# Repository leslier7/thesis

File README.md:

# A Comparison of the Arm and RISC-V Architectures on the RP2350 Microcontroller

## Abstract
This thesis compares the M-33 implementation of the Arm ISA with the Hazard3
implementation of the RISC-V ISA on the RP2350 microcontroller chip. It details why this chip, containing two different cores, presents unique opportunities to
learn about their implementation. The two implementations are compared. Custom benchmarks were developed, and existing benchmarks were ported to the Pico
platform to collect performance, power consumption, and binary data about both
core implementations. Our results show that, although ARM benefits from specialized hardware, both implementations perform similarly on real-world benchmarks,
depending on the task. A copy of this thesis is available via the [Lafayette College Digital Repository](https://ldr.lafayette.edu/concern/student_works/cv43nz485)

This repository contains the source code for the thesis. It also contains Python scripts used for data collection, and the PCB design files for the testing board.

## Instructions for Building Pico Benchmarks

### Requirements

- [Pico SDK](https://github.com/raspberrypi/pico-sdk)
- A RISC-V toolchain [(Like CoreV)](https://embecosm.com/downloads/tool-chain-downloads/#core-v-top-of-tree-compilers)

### Building the Benchmarks
To build the benchmarks, you will need to set up the Pico SDK and the RISC-V toolchain. Then follow these steps:
- Clone the repository: `git clone https://github.com/leslier7/thesis.git`
- Navigate to the benchmark directory that you want to build, e.g., `cd thesis/floatmark`
- Make a build directory and navigate into it: `mkdir build-arm && cd build-arm` or `mkdir build-riscv && cd build-riscv`
- Run CMake to configure the build:
  - For Arm: <pre> ```cmake .. -DPICO_PLATFORM=rp2350 -DARCH=arm ``` </pre>
  - For RISC-V: <pre> ```cmake .. -DPICO_PLATFORM=rp2350-riscv -DARCH=risc ``` </pre>
- Then build the benchmark with: <pre> ```make``` </pre>
- Do this for each benchmark you want to build.

### Running the Benchmarks
- Upload the resulting `.uf2` files to the Pico 2 board by dragging and dropping them onto the board when it is in bootloader mode (hold the BOOTSEL button while plugging in the MicroUSB cable).
- The benchmark will automatically run when the board is powered on. It will output the results to the serial port, which can be read using a terminal program or the provided Python scripts.
  - The TestingPCB has a USB-C port for connecting a serial adapter to a computer 

## Instructions for Running the Scripts

### Requirements
- Python 3.x with the following packages:
  - `numpy`
  - `serial`
  - `csv`
- A Nordic Semi Power Profiler II power measurement device (if measuring power consumption)

### Running the UART Script
- Connect the USB-C port on the testing board to your computer.
- Run the script: <pre> ```python UartScript.py file_name.csv port_name``` </pre>
  - Replace `file_name.csv` with the desired output file name (it can be a path).
  - Replace `port_name` with the serial port name (e.g., `/dev/ttyUSB0` on Linux).
- Plug the Micro-USB cable into the Pico 2 board to power it on.
- Unplug and replug the Micro-USB cable to reset the board 10 times to fully test each benchmark.
  - If using the PPK2 to measure the power consumption, toggle the power source in the software 10 times instead.

### Collecting Power Measurements
- Follow the instructions in `Section 4.3.2.4` of the thesis to set up the PPK2 and collect power measurements.

### Running the Power Measurement Script
- Make sure that you have exported the data from the PPK2 software to a CSV file following the instructions in section 4.3.2.4 of the thesis.
- Run the script: <pre> ```python ChargeScript.py folder_path``` </pre>
  - Replace `folder_path` with the top level folder containing the CSV files exported from the PPK2 software. It will process all CSV files in all subfolders and put the outputs of each folder in an `Outputs` folder.

## Instructions for the PCB Design Files
The PCB design files are located in the `TestingPCB` directory. They were created using KiCad8. To view or modify them, you will need to install KiCad and open the `.kicad_pro` project file.

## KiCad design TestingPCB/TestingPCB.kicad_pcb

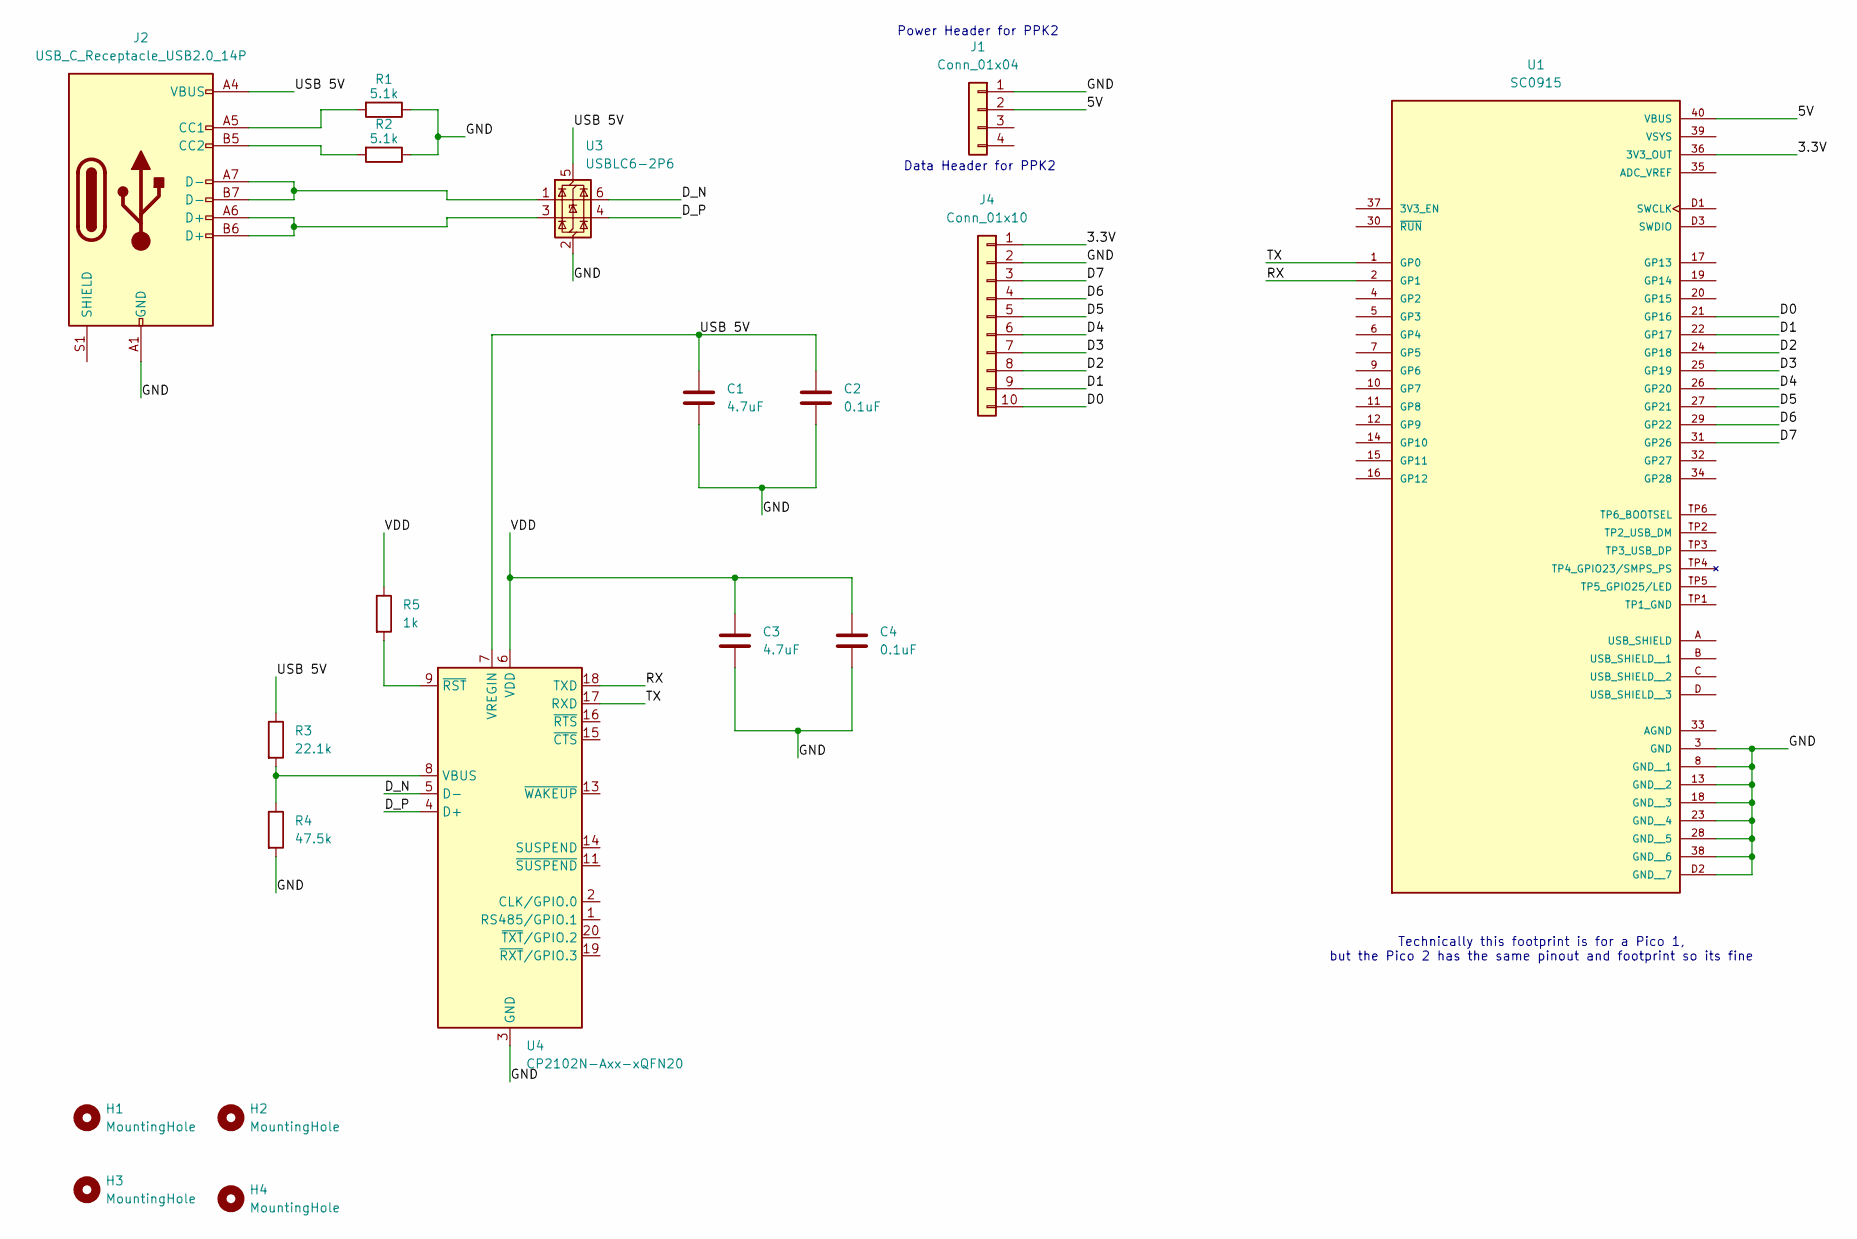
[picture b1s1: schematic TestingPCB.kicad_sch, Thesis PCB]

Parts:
C1, C3: 4.7uF; C_1206_3216Metric; Manufacturer Part Number CL31B475KOHNNNE
C2, C4: 0.1uF; C_1206_3216Metric; Manufacturer Part Number C1206C104K5RACTU
H1, H2, H3, H4: MountingHole; MountingHole_3.2mm_M3_ISO7380_Pad_TopBottom
J1: Conn_01x04; Harwin_M20-89004xx_1x04_P2.54mm_Horizontal; Manufacturer Part Number M20-8900405
J2: USB_C_Receptacle_USB2.0_14P; USB_C_Receptacle_GCT_USB4105-xx-A_16P_TopMnt_Horizontal; Manufacturer Part Number USB4105-GF-A
J4: Conn_01x10; HARWIN_M20-8891045; Manufacturer Part Number M20-8891045
R1, R2: 5.1k; R_1206_3216Metric; Manufacturer Part Number CRCW12065K10FKEA
R3: 22.1k; R_1206_3216Metric; Manufacturer Part Number RNCP1206FTD22K1
R4: 47.5k; R_1206_3216Metric; Manufacturer Part Number RC1206FR-0747K5L
R5: 1k; R_1206_3216Metric; Manufacturer Part Number RNCP1206FTD1K00
U1: SC0915; pico; PARTREV 1.9
U3: USBLC6-2P6; SOT-666; Manufacturer Part Number USBLC6-2P6
U4: CP2102N-Axx-xQFN20; SiliconLabs_QFN-20-1EP_3x3mm_P0.5mm_EP1.8x1.8mm; Manufacturer Part Number CP2102N-A02-GQFN20R

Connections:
/3.3V: J4.1, U1.36 (3V3_OUT)
/5V: J1.2, U1.40 (VBUS)
/D0: J4.10, U1.21 (GP16)
/D1: J4.9, U1.22 (GP17)
/D2: J4.8, U1.24 (GP18)
/D3: J4.7, U1.25 (GP19)
/D4: J4.6, U1.26 (GP20)
/D5: J4.5, U1.27 (GP21)
/D6: J4.4, U1.29 (GP22)
/D7: J4.3, U1.31 (GP26)
/D_N: U3.6 (I/O1), U4.5 (D-)
/D_P: U3.4 (I/O2), U4.4 (D+)
/GND: C1.2, C2.2, C3.2, C4.2, J1.1, J2.A1 (GND), J2.A12 (GND), J2.B1 (GND), J2.B12 (GND), J4.2, R1.1, R2.1, R4.2, U1.3 (GND), U1.8 (GND__1), U1.13 (GND__2), U1.18 (GND__3), U1.23 (GND__4), U1.28 (GND__5), U1.38 (GND__6), U1.D2 (GND__7), U3.2 (GND), U4.3 (GND), U4.12 (GND), U4.21 (GND)
/RX: U1.2 (GP1), U4.18 (TXD)
/TX: U1.1 (GP0), U4.17 (RXD)
/USB 5V: C1.1, C2.1, J2.A4 (VBUS), J2.A9 (VBUS), J2.B4 (VBUS), J2.B9 (VBUS), R3.1, U3.5 (VBUS), U4.7 (VREGIN)
/VDD: C3.1, C4.1, R5.1, U4.6 (VDD)
unnamed: J2.A5 (CC1), R1.2
unnamed: J2.B5 (CC2), R2.2
unnamed: J2.A6 (D+), J2.B6 (D+), U3.3 (I/O2)
unnamed: J2.A7 (D-), J2.B7 (D-), U3.1 (I/O1)
unnamed: R3.2, R4.1, U4.8 (VBUS)
unnamed: R5.2, U4.9 (~RST)

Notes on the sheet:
Data Header for PPK2
Technically this footprint is for a Pico 1, but the Pico 2 has the same pinout and footprint so its fine
Power Header for PPK2

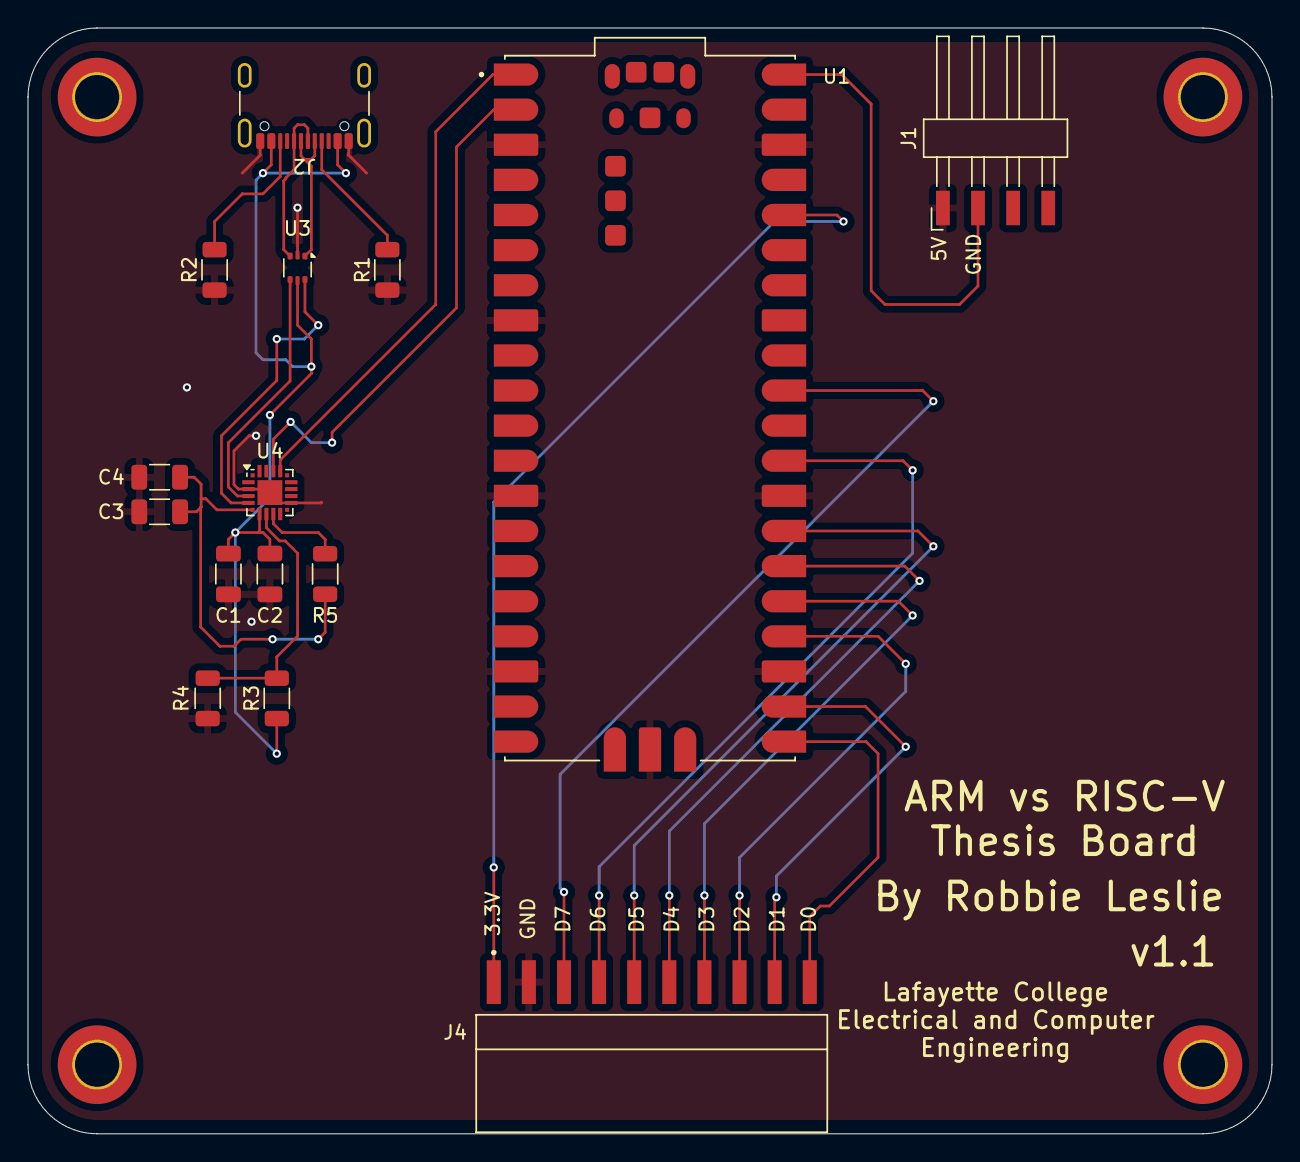
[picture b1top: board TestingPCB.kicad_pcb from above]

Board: 2 copper layers, 90.0 x 80.0 mm, 19 parts (0 on the bottom side), 23 nets.

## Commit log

2024-09-11 Added README
2024-09-12 Initial tests, including vscode extension
2024-09-18 Added BlinkLEDArch
2024-09-19 Updated .gitignore
2024-09-25 Read from the register to see which architecture is running
2024-09-25 Updated CMmake to not specify PICO_PLATFORM and gitignore
2024-09-25 Changed accessing the register with hardware_structs
2024-10-09 Got print working and added basicmath from MiBench
2024-10-23 Changed basicmath and got bitcount working
2024-10-29 Added qsort and low power mode at the end of benchmarks
2024-11-06 Changed doubles to floats to check assembly
2024-11-07 Got FFT running
2024-11-07 Started working on getting instruction count
2024-11-07 Added powman
2024-11-14 Started work on cycle count for ARM' q
2024-11-14 Potentially added clock cycles to basicmath
2024-11-14 Added debug mode to turn off optimizaitons
2024-11-14 Added instruction count but missing 2 registers
2024-11-14 Initial version of CoreMark
2024-11-15 Got CoreMark printing
2024-11-21 Got instruction count working for ARM
2024-11-21 Updated way of differentiating architecture in CMake
2024-12-04 Added new project to test things in, and used GPIO pin to measure power
2024-12-06 Worked on RISC instruction counts, although right now it doesn't work/crashes program
2024-12-14 Got serial working over usb
2025-02-03 Added IDE settings
2025-02-03 Added test print statements
2025-02-05 More tests to try and get the register reading
2025-02-05 Testing using assembly to read and write to CSRs
2025-02-07 Got some of it working, but too many instructions
2025-02-07 Got instruction count working
2025-02-19 Started work on floatmark and added GPIO power measurment functions
2025-02-24 Initial version of floatMark
2025-02-24 Cleaned up Coremark and added idea files
2025-02-25 Updating benchmark
2025-02-25 Updated CMake to build both o3 and o0 versions of the code
2025-02-26 Initial PCB schematic
2025-02-26 v1 of PCB
2025-02-26 Updated gitignore
2025-02-26 Updated silkscreen
2025-03-04 Testing bugs with doublemark
2025-03-05 Testing floating division overflow
2025-03-05 Fixed division overflow
2025-03-10 Started swapping to 10 pin logic connector
2025-03-10 Updated to testing mode
2025-03-10 Updated PCB with 10 pin logic connector
2025-03-10 Added script to read the charge from the PPK2 CSV files
2025-03-10 Updated to use the 20 pin package and fixed power for CP2102N
2025-03-12 Updated ChargeScript to output to CSV, floatmark to end, started work on FloatmarkUart
2025-03-12 Updated scripts
2025-03-13 Working on adding start benchmakr power measurements
2025-03-23 Updated BOM
2025-03-26 Updated script to look at every CSV file in a folder
2025-03-26 Updated to group by tests to more easily copy data
2025-03-26 Updated number of tests in serial script
2025-03-26 Updated serial script and added script to reorganize data csvs
2025-03-27 Fixed ChargeScript any typo in print statements
2025-03-28 Updated basicmath with new testing procedures
2025-03-28 Added ide file
2025-04-01 Started work on bitcount conversion
2025-04-01 Got most of the benchmarks building
2025-04-01 Coremark error
2025-04-04 Got coremark working with RISC, and updated with new method
2025-04-08 Added coremark IDE settings
2025-04-08 Added sub benchmarks for floatmark
2025-04-08 Added doublemark benchmarks
2025-04-08 Fixed power pinout
2025-04-10 Ignore results
2025-04-10 Updated basicmath ide files and changed uart script
2025-04-10 Renamed binaries and print file at end of UART script
2025-04-11 Added end of benchmark to coremark
2025-04-13 Updated bitcount print results
2025-04-13 Updated ide cmake settings for bitcount
2025-04-13 Updated print statements and fixed bitcount cmake
2025-04-23 Added overflow detector
2025-04-30 Updated for overflow testing
2025-05-05 Updated Coremark Arm build to align with other builds
2025-05-07 Added Intmark
2025-05-28 Updated coremark to fix portme
2025-07-22 Updated the README with a better project description
2025-08-11 Added openocd file for debugging
2025-08-11 Added launch file for real this time
2025-08-27 Improve code formatting in README.md
    Updated command formatting in README for clarity.
